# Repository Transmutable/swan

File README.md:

# Swan has moved

Hello, Trevor here.

I've moved my repositories over to Codeberg, a nice new host for open projects.

Here we go: [Codeberg.org/Transmutable/swan](https://codeberg.org/Transmutable/swan)

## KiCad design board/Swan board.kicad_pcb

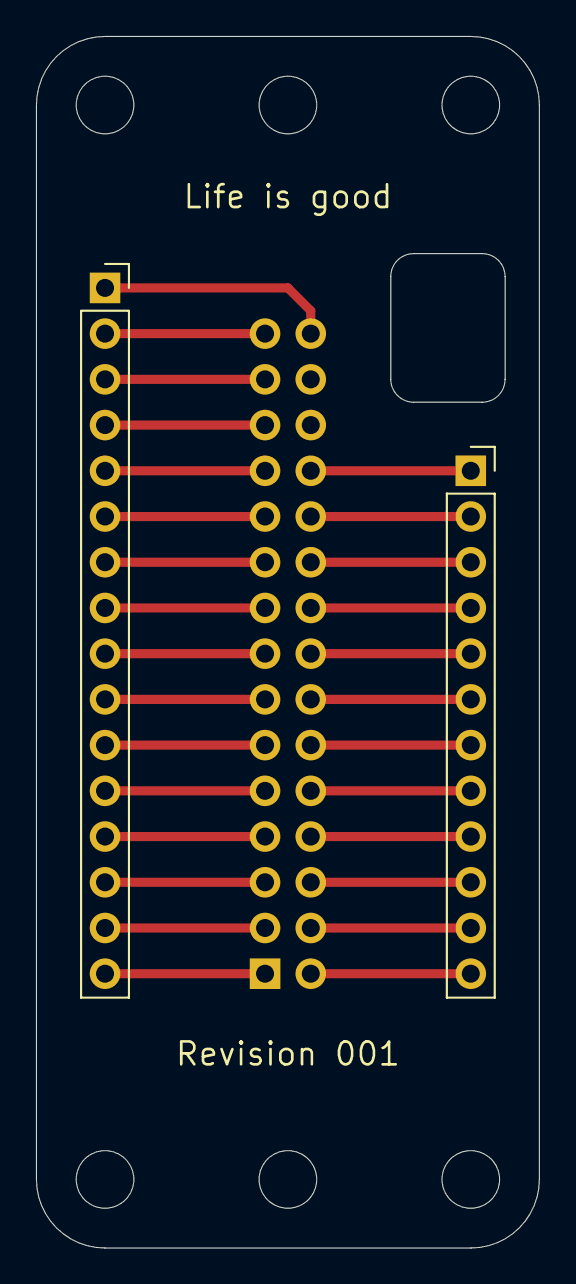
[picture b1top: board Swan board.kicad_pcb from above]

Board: 2 copper layers, 27.9 x 67.3 mm, 9 parts (1 on the bottom side), 28 nets.

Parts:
H1, H2, H3, H4, H5, H6: MountingHole; MountingHole_3.2mm_M3
J1: Conn_01x16_Female; PinSocket_1x16_P2.54mm_Vertical
J2: Conn_01x12_Female; PinSocket_1x12_P2.54mm_Vertical
J3: Conn_02x15_Odd_Even; PinHeader_2x15_P2.54mm_Vertical

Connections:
unnamed: J1.1, J3.30
unnamed: J1.2, J3.29
unnamed: J1.3, J3.27
unnamed: J1.4, J3.25
unnamed: J1.5, J3.23
unnamed: J1.6, J3.21
unnamed: J1.7, J3.19
unnamed: J1.8, J3.17
unnamed: J1.9, J3.15
unnamed: J1.10, J3.13
unnamed: J1.11, J3.11
unnamed: J1.12, J3.9
unnamed: J1.13, J3.7
unnamed: J1.14, J3.5
unnamed: J1.15, J3.3
unnamed: J1.16, J3.1
unnamed: J2.1, J3.24
unnamed: J2.2, J3.22
unnamed: J2.3, J3.20
unnamed: J2.4, J3.18
unnamed: J2.5, J3.16
unnamed: J2.6, J3.14
unnamed: J2.7, J3.12
unnamed: J2.8, J3.10
unnamed: J2.9, J3.8
unnamed: J2.10, J3.6
unnamed: J2.11, J3.4
unnamed: J2.12, J3.2

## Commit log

2021-04-27 Add the CAD files.
2021-04-27 Add STLs
2021-04-28 Updated README and wrote the BOM.
2021-04-28 Tweak.
2021-09-04 Added an example script: love letters
2024-04-19 Put up the we-moved sign
